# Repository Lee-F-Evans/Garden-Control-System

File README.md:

# Garden-Control-System
Problem statement: With building concerns around food and air quality and its health implications, more people are learning the basics of agriculture and trying their hand at growing their own food or house plants for natural air filtering. Many people are finding that this is a tricky and tedious process requiring the sacrice of many plants in the learning process. This control board aims to improve the success rate for beginers and give experts the metrics they need to optimize plant health and food independance. Currently there is a hole in the market for a product such as this.  

## Features
**Garden scheduling:** schedule lights or watering periods

**Software metrics:** Plant suitability based on time of year, temperature, humidity, light intensity, growth cycle, or personal care preferences.

**Web Based Interface**: View data and other reports and control your garden from a website.

**Power Monitoring:** Monitor the power usage of your system for a detailed breakdown on how much your set is going to cost to operate and whether or not a solar powered option will be suitable for you.

**Data collection:** View temperatures, water/soil quality, light intensity and more metrics that can be used for plant selection, planning routine care or maintenance, selecting location or your hardware setup such as lights, fans and heaters.

**Reports:** Daily, weekly or monthly reports on data metrics or anticipated weather events to avoid disasters like hail taking out your garden!

## Software
- Python module for communicating with the board over TCP/UDS
- Run a webiste to report metrics and provide additional features useful for gardening

## Firmware
- Firmware for controlling the board, setting power limitations, reporting data, etc.
- Smart control for scheduling pumps and lights, controlling fans to hit a target humidity, reporting dangerous conditions for plants 
## Hardware
- STM32 MCU for hardware control and data processing and sending to a host computer or server
- Motor drivers for fans and pumps 
- Sensors
  - Ambient temperature
  - Water/Soil temperature
  - Current and voltage monitoring for the system supply and each motor driver channel
  - Light sensors (light dependant resistors or better sensors?)
  - Water quality monitoring for TDS and pH
  - Humidity sensor
- Display for temp, light and power graphs and reporting water quality

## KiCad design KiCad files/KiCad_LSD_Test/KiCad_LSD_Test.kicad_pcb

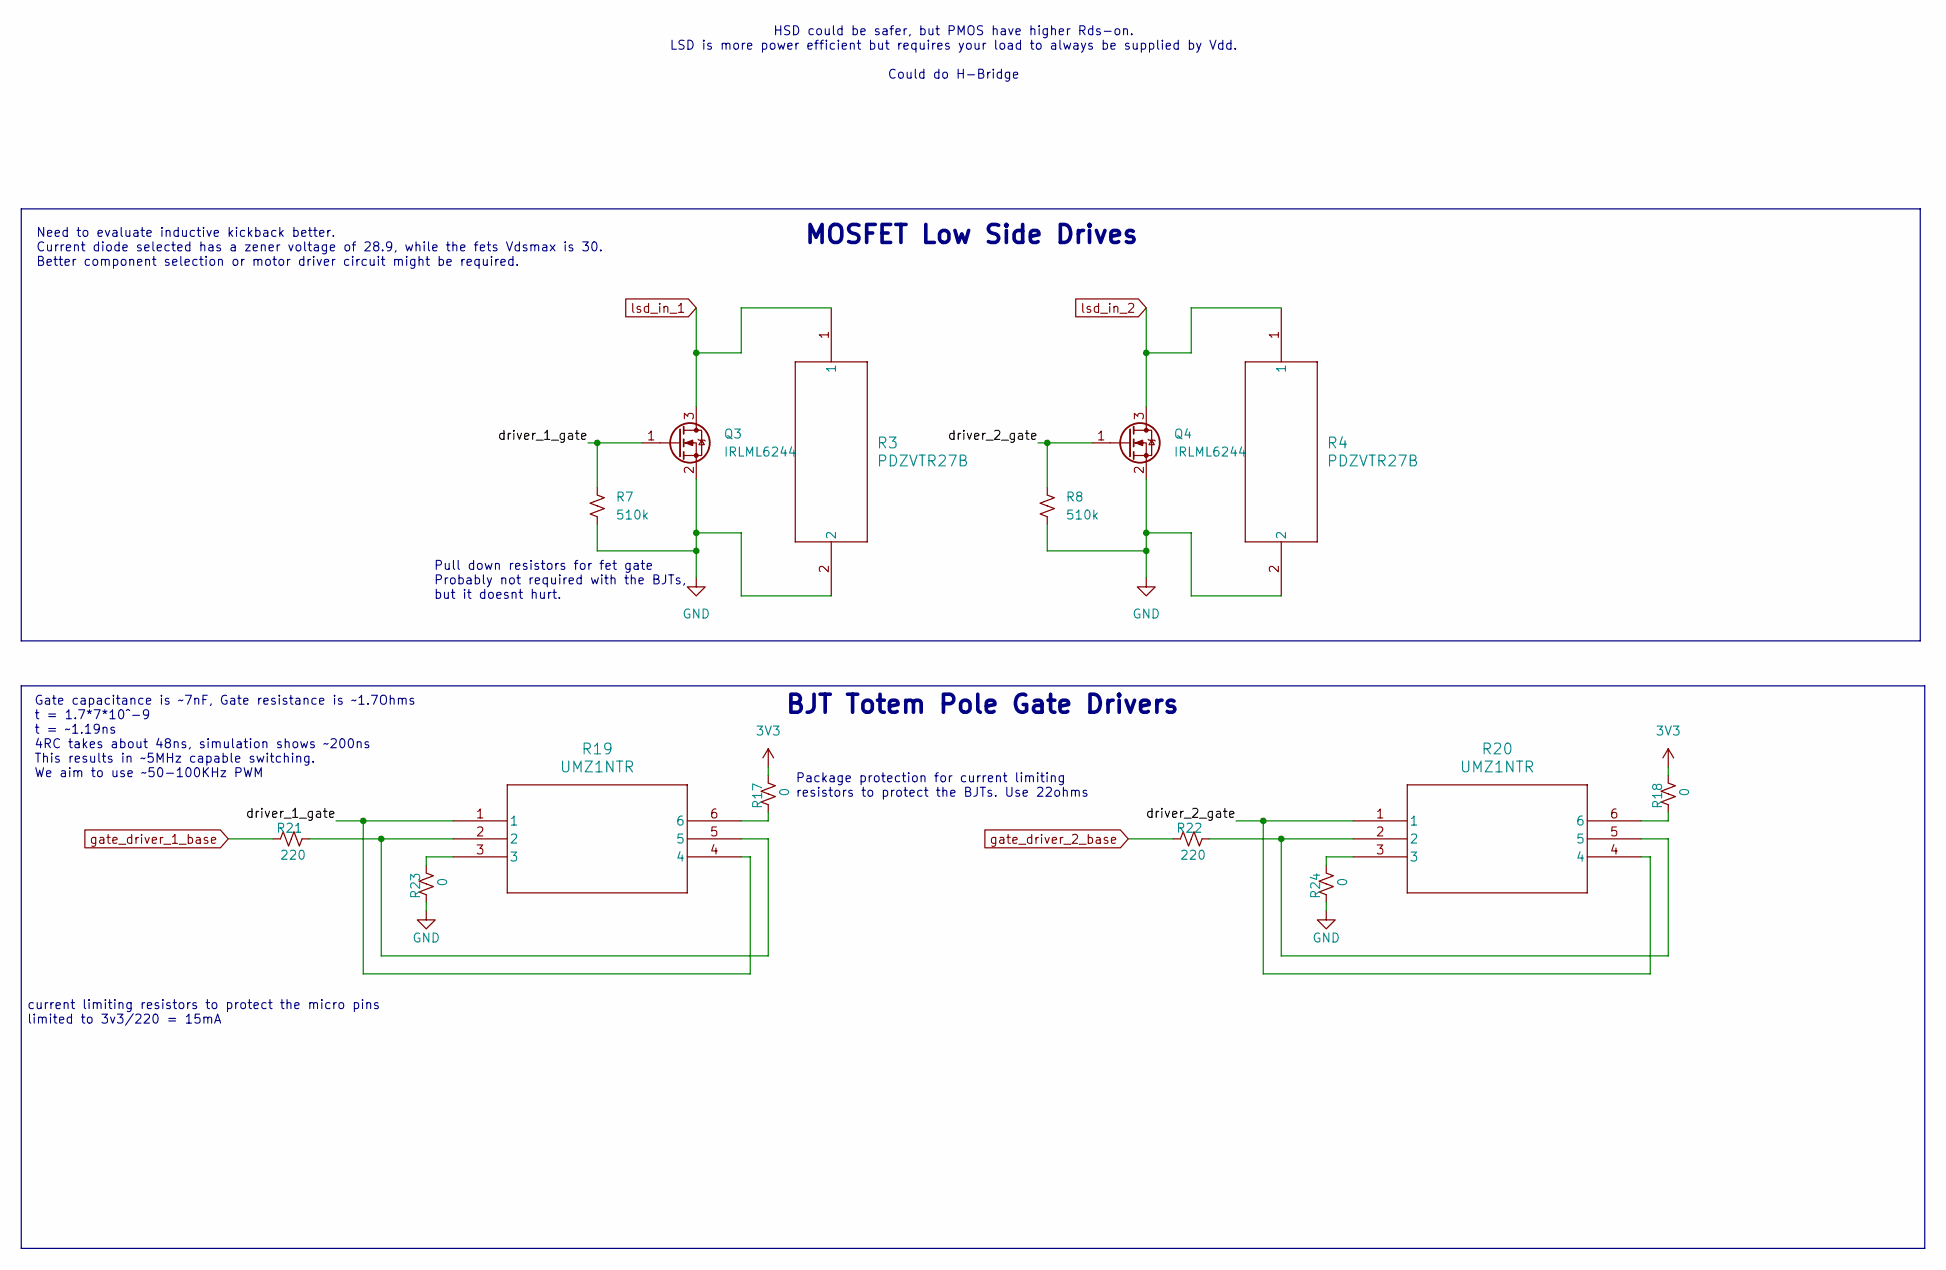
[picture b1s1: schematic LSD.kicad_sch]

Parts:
Q3, Q4: IRLML6244; SOT-23
R3, R4: PDZVTR27B; DIO_PDZVTFT_ROM
R7, R8: 510k; LED_0805_2012Metric_Pad1.15x1.40mm_HandSolder
R17, R18, R23, R24: 0; C_0805_2012Metric_Pad1.18x1.45mm_HandSolder
R19, R20: UMZ1NTR; TRANS_UM6J1_ROM
R21, R22: 220; C_0805_2012Metric_Pad1.18x1.45mm_HandSolder

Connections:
3V3: R17.2, R18.2; also elsewhere on the board
/LSD/driver_1_gate: Q3.1 (G), R7.1, R19.1, R19.4
/LSD/driver_2_gate: Q4.1 (G), R8.1, R20.1, R20.4
GND: Q3.2 (S), Q4.2 (S), R3.2, R4.2, R7.2, R8.2, R23.1, R24.1; also elsewhere on the board
unnamed: R17.1, R19.6
unnamed: R18.1, R20.6
unnamed: R19.2, R19.5, R21.2
unnamed: R19.3, R23.2
unnamed: R20.2, R20.5, R22.2
unnamed: R20.3, R24.2
gate_driver_1_base: R21.1; also elsewhere on the board
gate_driver_2_base: R22.1; also elsewhere on the board
lsd_in_1: Q3.3 (D), R3.1; also elsewhere on the board
lsd_in_2: Q4.3 (D), R4.1; also elsewhere on the board

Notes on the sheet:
Gate capacitance is ~7nF, Gate resistance is ~1.7Ohms t = 1.7*7*10^-9 t = ~1.19ns 4RC takes about 48ns, simulation shows ~200ns This results in ~5MHz capable switching. We aim to use ~50-100KHz PWM
Need to evaluate inductive kickback better. Current diode selected has a zener voltage of 28.9, while the fets Vdsmax is 30. Better component selection or motor driver circuit might be required.
HSD could be safer, but PMOS have higher Rds-on. LSD is more power efficient but requires your load to always be supplied by Vdd. Could do H-Bridge
Pull down resistors for fet gate Probably not required with the BJTs, but it doesnt hurt.
MOSFET Low Side Drives
Package protection for current limiting resistors to protect the BJTs. Use 22ohms
current limiting resistors to protect the micro pins limited to 3v3/220 = 15mA
BJT Totem Pole Gate Drivers

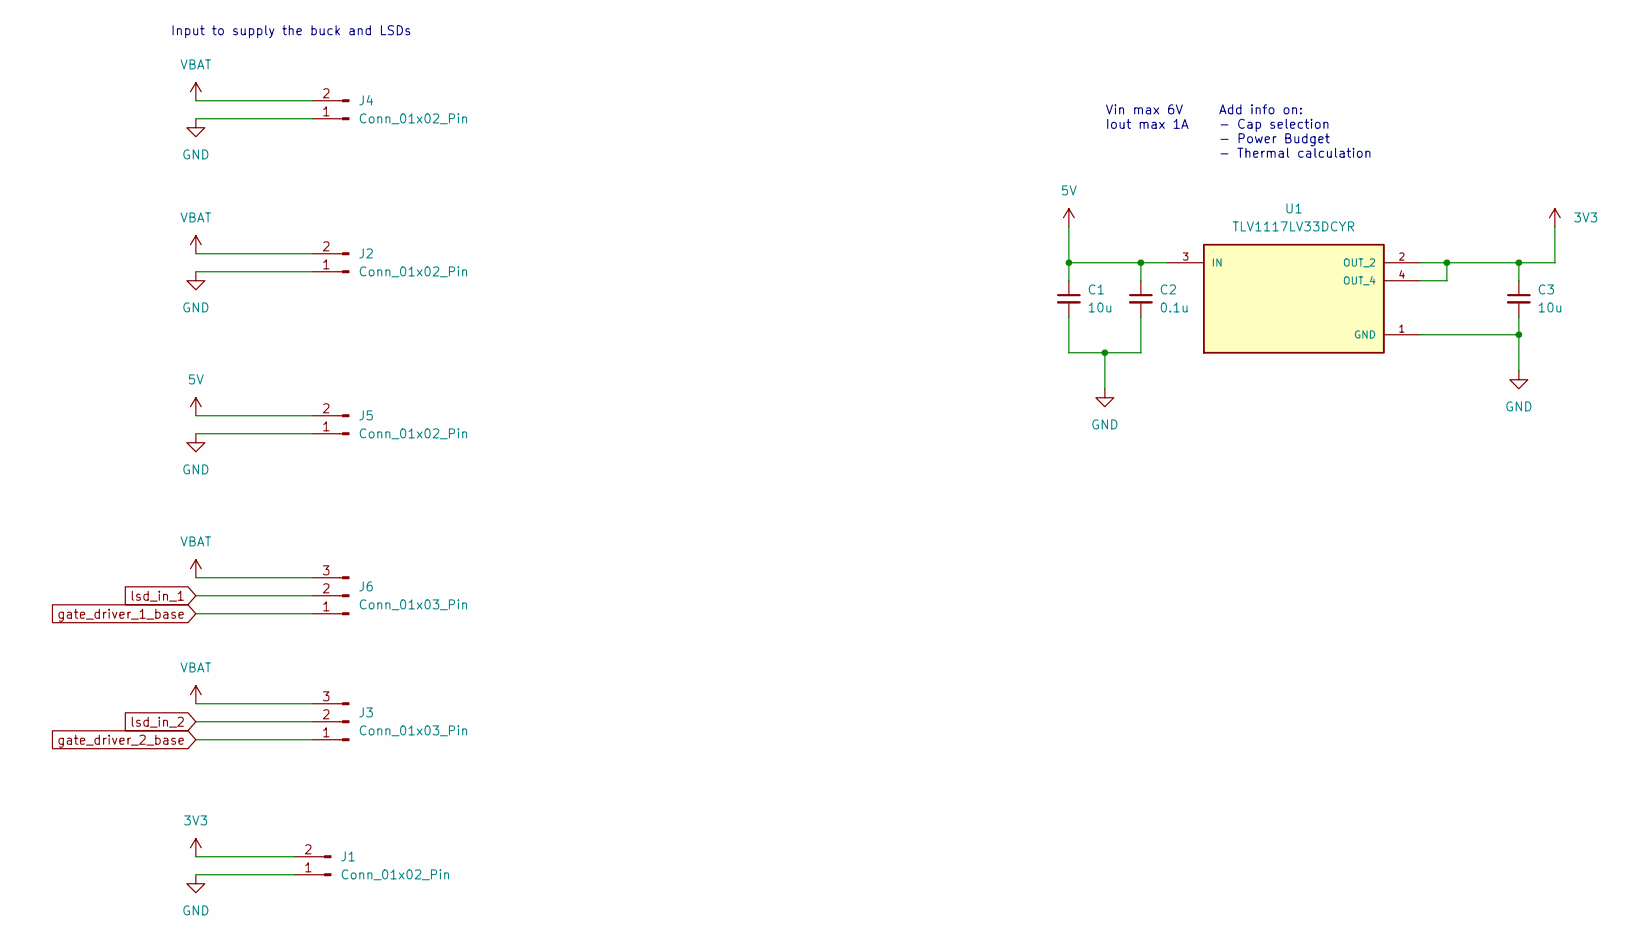
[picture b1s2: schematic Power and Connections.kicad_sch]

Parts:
C1, C3: 10u; C_0805_2012Metric_Pad1.18x1.45mm_HandSolder
C2: 0.1u; C_0805_2012Metric_Pad1.18x1.45mm_HandSolder
J1, J2, J4, J5: Conn_01x02_Pin; PinHeader_1x02_P1.00mm_Vertical
J3, J6: Conn_01x03_Pin; PinHeader_1x03_P1.00mm_Vertical
U1: TLV1117LV33DCYR; VREG_TLV1117LV33DCYR; PARTREV B

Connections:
3V3: C3.1, J1.2, U1.2 (OUT_2), U1.4 (OUT_4); also elsewhere on the board
5V: C1.1, C2.1, J5.2, U1.3 (IN)
GND: C1.2, C2.2, C3.2, J1.1, J2.1, J4.1, J5.1, U1.1 (GND); also elsewhere on the board
VBAT: J2.2, J3.3, J4.2, J6.3
gate_driver_1_base: J6.1; also elsewhere on the board
gate_driver_2_base: J3.1; also elsewhere on the board
lsd_in_1: J6.2; also elsewhere on the board
lsd_in_2: J3.2; also elsewhere on the board

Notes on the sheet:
Input to supply the buck and LSDs
Add info on: - Cap selection - Power Budget - Thermal calculation
Vin max 6V Iout max 1A

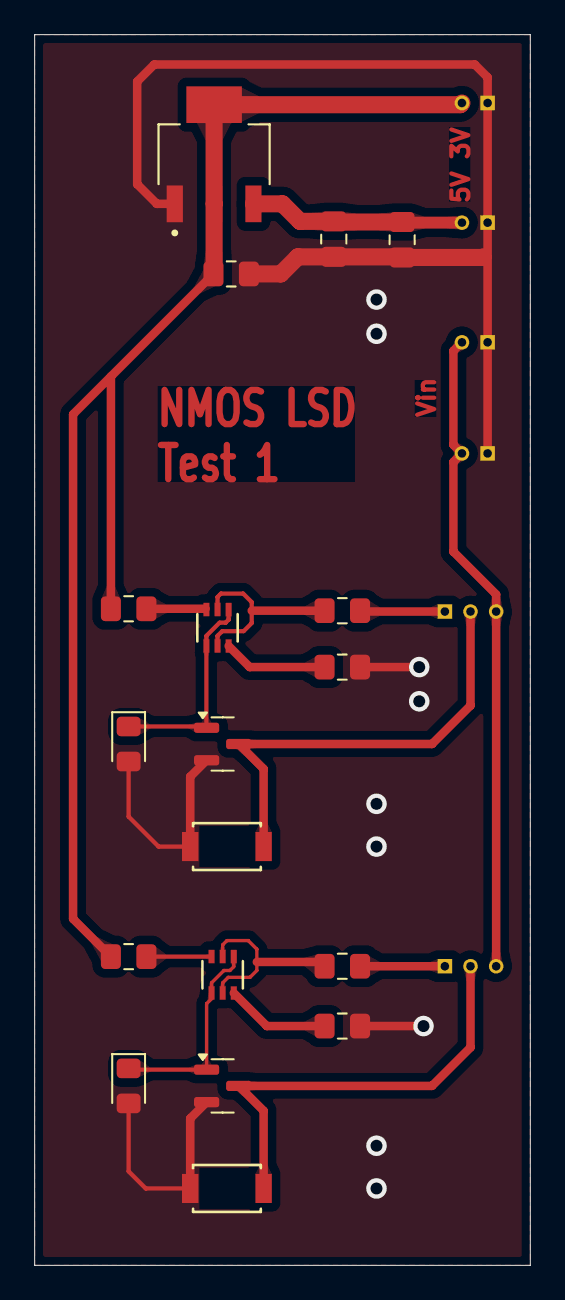
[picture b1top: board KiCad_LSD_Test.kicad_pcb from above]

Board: 2 copper layers, 29.0 x 72.0 mm, 24 parts (0 on the bottom side), 16 nets.

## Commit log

2024-04-07 Add files via upload
    First upload
2024-04-08 Close to finishing ethernet side
2024-04-08 working on power arch
2024-04-09 working on gate driver circuit for motor control
2024-04-09 expanded power supply section. completed LSD design. sized shunt resistors
2024-04-10 made changes to stmcube project
2024-04-23 adding recent schematic progress
2024-04-26 working on temp sensor circuit
2024-04-29 added more info to temp section
2024-05-14 updating any minor changes
2024-07-28 saving changes
2024-07-29 Added a basic readme
2024-11-08 we cookin' again. Added LSD and start temp sense section.
2024-11-08 we cookin'
